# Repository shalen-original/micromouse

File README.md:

# Micromouse WiSe2021

## Project members:

* Philipp Hagenlocher
* Hendrik Möller
* Matteo Nardini
* Congnan "Jonas" Wang

## Goal and milestone:
The goal of this project is to build a micromouse from scatch and solve the maze challenge offerred by TUM. 

- [x] **22. Febuary: board design review** 
- [x] **1. March: board design fixed**
- [ ] **10.March: board ready**
- [ ] **31.March: project finshed**

## Maze definition:
>The micromouse maze shall comprise **16 x 16** multiples of an **18cm x 18cm** unit square.
The walls constituting the micromouse maze shall be **5cm high** and **1.2cm thick**. 

According to UK Micromouse Maze Solver Rules:
<https://www.cs.york.ac.uk/micromouse/Rules/Maze_Solver_Rules.pdf>

## Project functionalities

* PCB Design
* Hardware Design
* HAL
* Closed Loop Control
* Maze-solver
* Communication and UI

## TODOs

#### PCB design:
- [ ] Understand voltage regulator thermal details and pick the one that are actually needed

#### Hardware design:
- [ ] Pick the distance sensors
- [ ] Pick the HBridges

#### HAL:
- [ ] To be filled

#### Closed Loop Control:
- [x] Classify controll scenarios
	* Straight: 3 scenarios
		* corridor
		* one side opening
		* both sides opening
	* Turn: switch off distance sensors
	* Spin: switch off distance sensors
- [x] Determine controller types
	* PI controller
- [x] Determine motionControl APIs
	* move (rawVelocity)
	* turn (rawVelocity)
	* spin (rawVelocity)
	* update (xxx)
- [ ] Coding controllers in c#
	* [x] connect controller to HAL
	* [x] build PI controller
	* [ ] impliment control logic
		* [x] distance controller
		* [x] velocity controller
		* [x] Lookup table for pwm 
		* [ ] update()
		* [ ] upper limit for accumulated error of controllers
		* [ ] Error notification in error.h
	* [x] wire motionControl.h API with controllers
- [ ] Theory for tuning controller parameters 
- [ ] Debug controller on board

#### Maze-solver
- [x] Classic Flood Fill

#### Communication and UI
- [ ] To be filled

# Code Notation/Styling:
```
* Name Formatting:
	- functions: camelCase - getSomething()
	- `#define: CAPSLOCK_WITH_UNDERSCORE - CONFIG_H`
	- Variables: camelCase - timerInterruptFrequency
* Use "init" instead of "setup" (if there is no difference)
* Use in-line brackets only for "} else {" or similiar lines
* Code-Comments in-line for single important statements (or declarations)
* Code-Comments before function headers in c-file
* One empty line between sections of code, ordered as follows:
	- Header file: 
		Guard condition, 
		includes, 
		`#defines (namespace)`
		extern variable declarations
		function headers
	- C file: 
		includes,
		`#define (for constants)`
		member variables
		function implementations

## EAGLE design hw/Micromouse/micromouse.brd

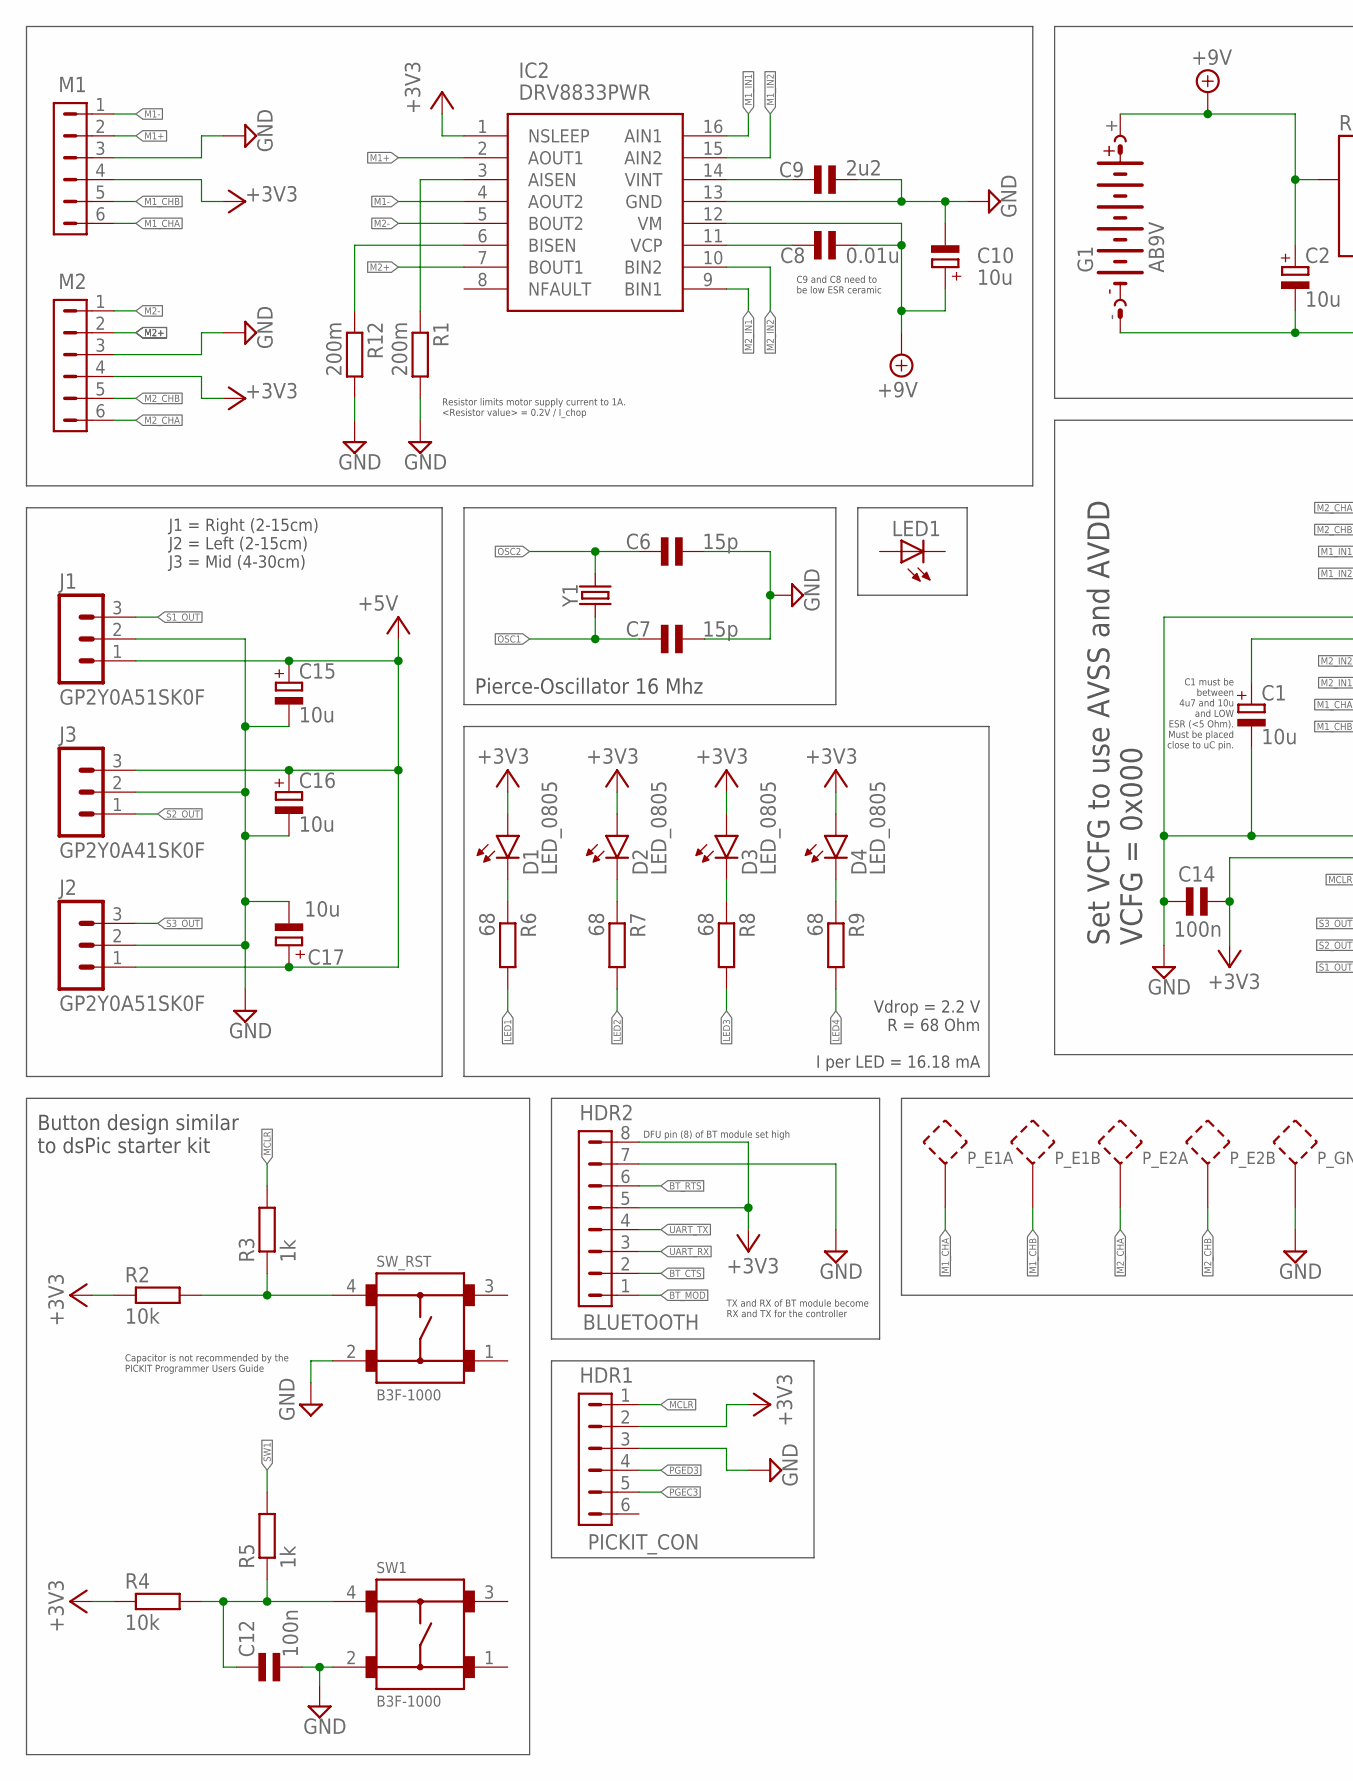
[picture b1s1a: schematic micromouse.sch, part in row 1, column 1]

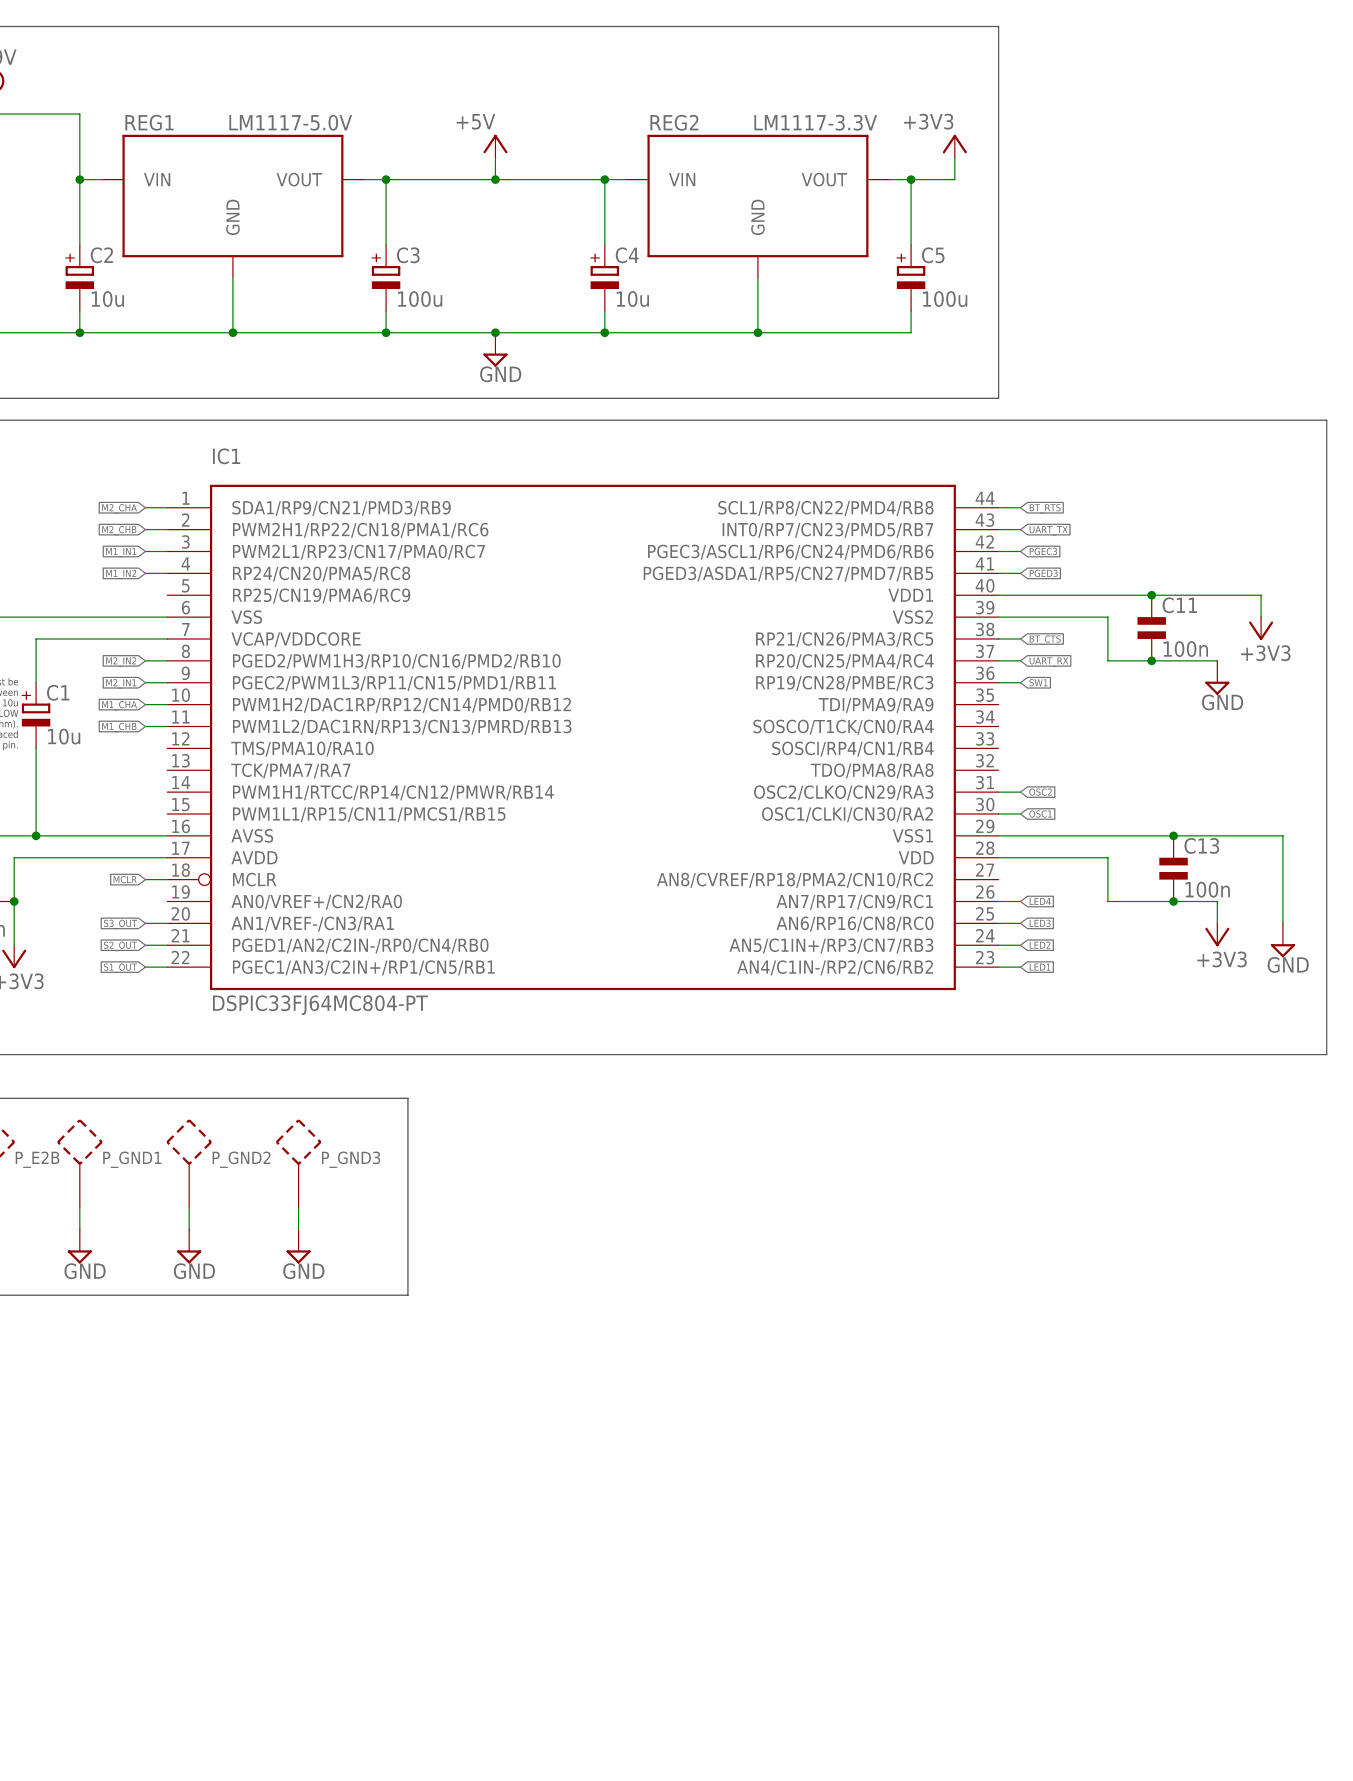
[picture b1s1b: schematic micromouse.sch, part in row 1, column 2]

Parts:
C1, C2, C4, C10, C15, C16, C17: 10u; 0805_POL
C3, C5: 100u; 0805_POL
C6, C7: 15p; 0805
C8: 0.01u; 0805
C9: 2u2; 0805
C11, C12, C13, C14: 100n; 0805
D1, D2, D3, D4: LED_0805; SMD_LED_0805
G1: AB9V
HDR1: PICKIT_CON; 6PIN
HDR2: BLUETOOTH; 1X08
IC1: DSPIC33FJ64MC804-PT; TQFP44
IC2: DRV8833PWR; SOP65P640X120-16N
J1, J2: GP2Y0A51SK0F; B3B-ZR(LF)(SN)
J3: GP2Y0A41SK0F; B3B-PH-K-S
LED1: LED5MM
M1, M2: MOTOR_CON; JP3Q
P_E1A, P_E1B, P_E2A, P_E2B: PROBE_POINTTHT; PROBEPOINT_THT
P_GND1, P_GND2, P_GND3: PROBE_POINTTHT; PROBEPOINT_THT
R1, R12: 200m; 0805
R2, R4: 10k; 0805
R3, R5: 1k; 0805
R6, R7, R8, R9: 68; 0805
REG1: LM1117-5.0V; SOT-223-4
REG2: LM1117-3.3V; SOT-223-4
SW1: B3F-1000
SW_RST: B3F-1000
Y1: CRYSTALPTH-HC49US; HC49US

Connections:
+3V3: C5.1 (+), C11.1 (+), C13.2 (-), C14.2 (-), D1.P$2 (A), D2.P$2 (A), D3.P$2 (A), D4.P$2 (A), HDR1.2, HDR2.5, HDR2.8, IC1.17 (AVDD), IC1.28 (VDD), IC1.40 (VDD1), IC2.1 (NSLEEP), M1.4, M2.4, R2.1, R4.1, REG2.2 (VOUT), REG2.4 (VOUT)
+5V: C3.1 (+), C4.1 (+), C15.1 (+), C16.1 (+), C17.1 (+), J1.1, J2.1, J3.3, REG1.2 (VOUT), REG1.4 (VOUT), REG2.3 (VIN)
+9V: C2.1 (+), C8.1 (+), C10.1 (+), G1.+, IC2.12 (VM), REG1.3 (VIN)
BT_CTS: HDR2.2, IC1.38 (RP21/CN26/PMA3/RC5)
BT_MOD: HDR2.1
BT_RTS: HDR2.6, IC1.44 (SCL1/RP8/CN22/PMD4/RB8)
GND: C1.2 (-), C2.2 (-), C3.2 (-), C4.2 (-), C5.2 (-), C6.2 (-), C7.2 (-), C9.2 (-), C10.2 (-), C11.2 (-), C12.2 (-), C13.1 (+), C14.1 (+), C15.2 (-), C16.2 (-), C17.2 (-), G1.-, HDR1.3, HDR2.7, IC1.6 (VSS), IC1.16 (AVSS), IC1.29 (VSS1), IC1.39 (VSS2), IC2.13 (GND), J1.2, J2.2, J3.2, M1.3, M2.3, P_GND1.P$1, P_GND2.P$1, P_GND3.P$1, R1.2, R12.2, REG1.1 (GND), REG2.1 (GND), SW1.2, SW_RST.2
LED1: IC1.23 (AN4/C1IN-/RP2/CN6/RB2), R6.2
LED2: IC1.24 (AN5/C1IN+/RP3/CN7/RB3), R7.2
LED3: IC1.25 (AN6/RP16/CN8/RC0), R8.2
LED4: IC1.26 (AN7/RP17/CN9/RC1), R9.2
M1+: IC2.2 (AOUT1), M1.2
M1-: IC2.4 (AOUT2), M1.1
M1_CHA: IC1.10 (PWM1H2/DAC1RP/RP12/CN14/PMD0/RB12), M1.6, P_E1A.P$1
M1_CHB: IC1.11 (PWM1L2/DAC1RN/RP13/CN13/PMRD/RB13), M1.5, P_E1B.P$1
M1_IN1: IC1.3 (PWM2L1/RP23/CN17/PMA0/RC7), IC2.16 (AIN1)
M1_IN2: IC1.4 (RP24/CN20/PMA5/RC8), IC2.15 (AIN2)
M2+: IC2.7 (BOUT1), M2.2
M2-: IC2.5 (BOUT2), M2.1
M2_CHA: IC1.1 (SDA1/RP9/CN21/PMD3/RB9), M2.6, P_E2A.P$1
M2_CHB: IC1.2 (PWM2H1/RP22/CN18/PMA1/RC6), M2.5, P_E2B.P$1
M2_IN1: IC1.9 (PGEC2/PWM1L3/RP11/CN15/PMD1/RB11), IC2.9 (BIN1)
M2_IN2: IC1.8 (PGED2/PWM1H3/RP10/CN16/PMD2/RB10), IC2.10 (BIN2)
MCLR: HDR1.1, IC1.18 (MCLR), R3.2
unnamed: IC2.6 (BISEN), R12.1
unnamed: D2.P$1 (C), R7.1
unnamed: C8.2 (-), IC2.11 (VCP)
unnamed: C9.1 (+), IC2.14 (VINT)
unnamed: IC2.3 (AISEN), R1.1
unnamed: C12.1 (+), R4.2, R5.1, SW1.4
unnamed: R2.2, R3.1, SW_RST.4
unnamed: D1.P$1 (C), R6.1
unnamed: D3.P$1 (C), R8.1
unnamed: D4.P$1 (C), R9.1
OSC1: C7.1 (+), IC1.30 (OSC1/CLKI/CN30/RA2), Y1.1
OSC2: C6.1 (+), IC1.31 (OSC2/CLKO/CN29/RA3), Y1.2
PGEC3: HDR1.5, IC1.42 (PGEC3/ASCL1/RP6/CN24/PMD6/RB6)
PGED3: HDR1.4, IC1.41 (PGED3/ASDA1/RP5/CN27/PMD7/RB5)
S1_OUT: IC1.22 (PGEC1/AN3/C2IN+/RP1/CN5/RB1), J1.3
S2_OUT: IC1.21 (PGED1/AN2/C2IN-/RP0/CN4/RB0), J3.1
S3_OUT: IC1.20 (AN1/VREF-/CN3/RA1), J2.3
SW1: IC1.36 (RP19/CN28/PMBE/RC3), R5.2
UART_RX: HDR2.3, IC1.37 (RP20/CN25/PMA4/RC4)
UART_TX: HDR2.4, IC1.43 (INT0/RP7/CN23/PMD5/RB7)
VCAP/VDDCORE: C1.1 (+), IC1.7 (VCAP/VDDCORE)

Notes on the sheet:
C1 must be between 4u7 and 10u and LOW ESR (<5 Ohm). Must be placed close to uC pin.
Pierce-Oscillator 16 Mhz
Resistor limits motor supply current to 1A. <Resistor value> = 0.2V / I_chop
Button design similar to dsPic starter kit
J1 = Right (2-15cm) J2 = Left (2-15cm) J3 = Mid (4-30cm)
Capacitor is not recommended by the PICKIT Programmer Users Guide
Set VCFG to use AVSS and AVDD VCFG = 0x000
TX and RX of BT module become RX and TX for the controller
DFU pin (8) of BT module set high
C9 and C8 need to be low ESR ceramic
Vdrop = 2.2 V R = 68 Ohm I per LED = 16.18 mA

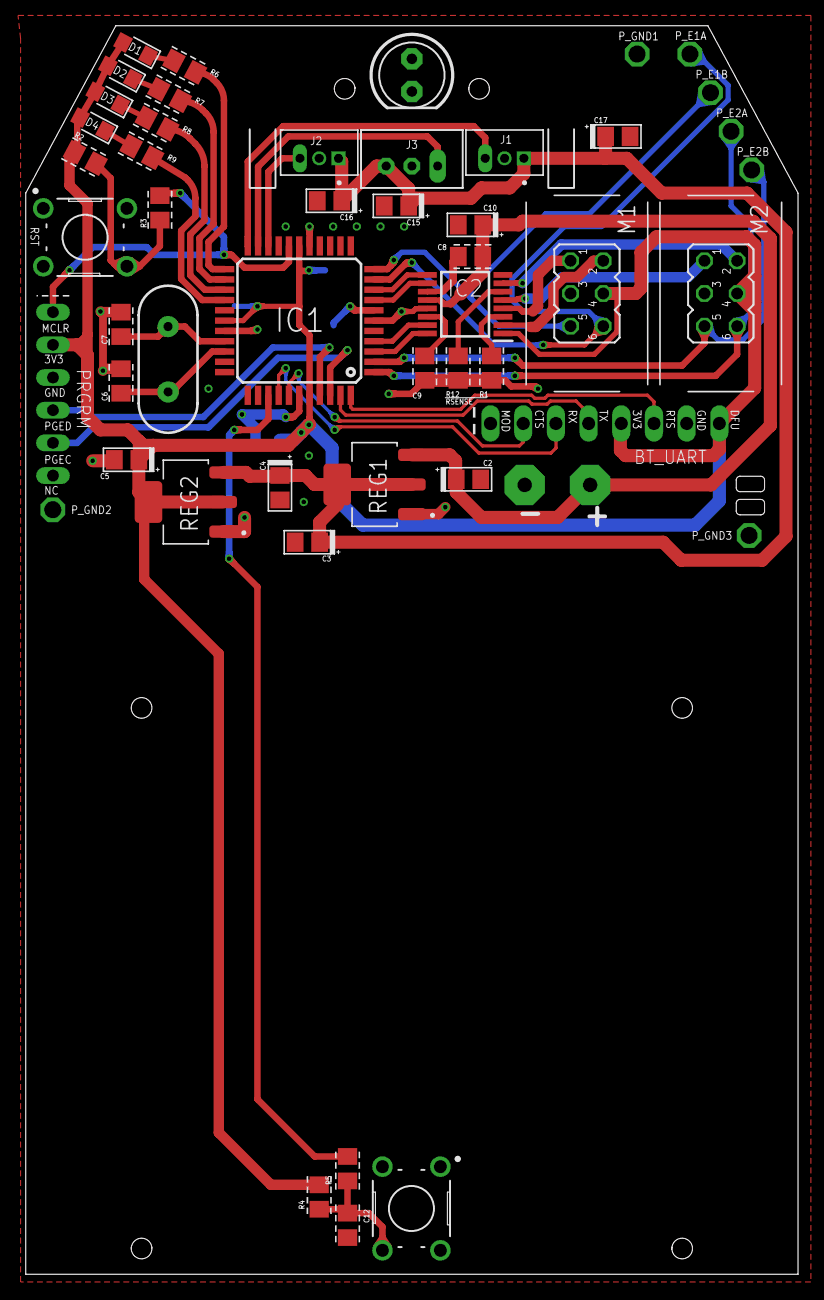
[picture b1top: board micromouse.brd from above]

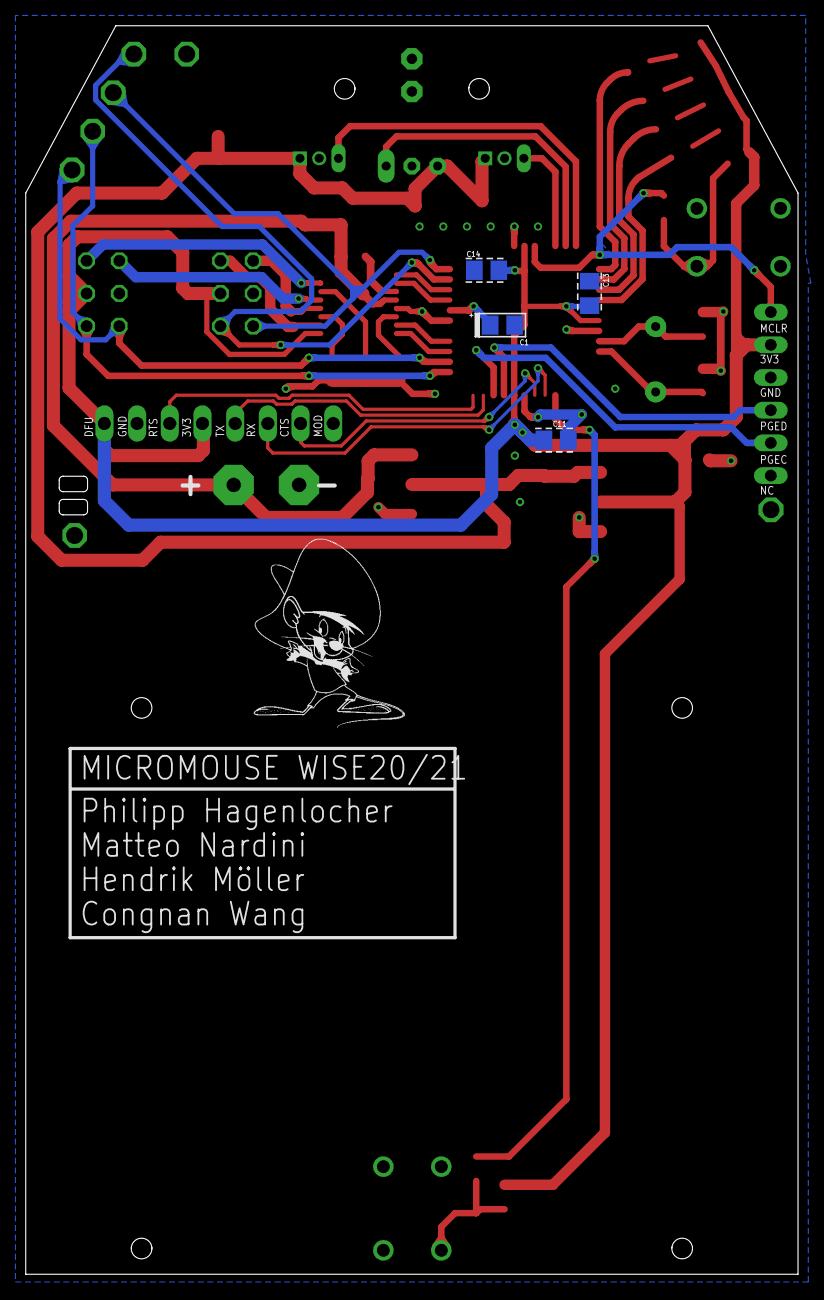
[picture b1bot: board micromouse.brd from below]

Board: 2 copper layers, 60.0 x 97.0 mm, 54 parts (4 on the bottom side), 44 nets.

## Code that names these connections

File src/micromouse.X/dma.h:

#ifndef DMA_H
#define	DMA_H

#include <xc.h>

#define RAW_SENSOR_RIGHT adcData[2]  // S1_OUT/AN3/RB1
#define RAW_SENSOR_FRONT adcData[1]  // S2_OUT/AN2/RB0
#define RAW_SENSOR_LEFT  adcData[0]  // S3_OUT/AN1/RA1

extern unsigned int adcData[32]__attribute__((space(dma)));

void initDMAChannel4(void);

#endif

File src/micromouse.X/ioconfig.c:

#include "xc.h"
#include "ioconfig.h"

void initIO()
{
    AD1PCFGL=0xFFFF; // Configure all pins to be digital
    
    // Configure the sensor pins to be analogue
    AD1PCFGLbits.PCFG1 = 0b0; // S3_OUT/AN1/RA1 is analougue
    AD1PCFGLbits.PCFG2 = 0b0; // S2_OUT/AN2/RB0 is analougue
    AD1PCFGLbits.PCFG3 = 0b0; // S1_OUT/AN3/RB1 is analougue
    
    // Configure the sensor pins to be input
    TRISAbits.TRISA1 = 0b1; // S3_OUT/AN1/RA1 is input
    TRISBbits.TRISB0 = 0b1; // S2_OUT/AN2/RB0 is input
    TRISBbits.TRISB1 = 0b1; // S1_OUT/AN3/RB1 is input
    
    // Configure LEDs to be outputs
    LATBbits.LATB2 = 0b0;
    LATBbits.LATB3 = 0b0;
    LATCbits.LATC0 = 0b0;
    LATCbits.LATC1 = 0b0;
    
    // Configure buttons to be inputs
    TRISCbits.TRISC3 = 0b1;
    
    // Remap pins (see tables 11-1 and 11-2 on the datasheet)
    __builtin_write_OSCCONL(OSCCON & 0xbf);
    
        // QEI1 -> Left Motor (M1)
        RPINR14bits.QEA1R = 12; //QEI1A -> RP12/M1_CHA
        RPINR14bits.QEB1R = 23; //QEI1B -> RP13/M1_CHB

        // QEI2 -> Right Motor (M2)
        RPINR16bits.QEA2R = 9; //QEI2A -> RP9/M2_CHA
        RPINR16bits.QEB2R = 22; //QEI2B -> RP22/M2_CHB

        // UART
        RPINR18bits.U1RXR = 20; //U1RX -> RP20/UART_RX
        RPINR18bits.U1CTSR = 21; //U1CTS -> RP21/BT_CTS
        RPOR3bits.RP7R = 0b00011; //U1TX -> RP7/UART_TX
        RPOR4bits.RP8R = 0b00100; //U1RTS -> RP8/BT_RTS
        
#ifdef SOFTWARE_FIX
        //Output compare
        RPOR11bits.RP23R = 0b10010; //OC1 -> RP23/M1_IN1
        RPOR12bits.RP24R = 0b10011; //OC2 -> RP24/M1_IN2
#endif

    __builtin_write_OSCCONL(OSCCON | 0x40);
     
    int i;
    for (i = 0; i < 30000; i++); // short dirty delay for changes to take effect
}

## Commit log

2021-01-13 Uploaded the draw.io hardware diagram
2021-01-16 Added EAGLE project
2021-01-16 Added BOM.ods
2021-01-18 Added voltage regulators and sensors to BOM
2021-01-18 Added JST PH components
2021-01-18 init first commit of MPLAB system added code styling (not finished!) to the README.md
2021-01-19 added mc_datasheet.pdf
2021-01-19 Added capacitors to BOM
2021-01-21 Added datasheets relating to oscillators
2021-01-21 Added voltage regulator circuit; Added oscillator configuration; Added parts to library
2021-01-21 moved mc_datasheet.pdf into datasheet folder
2021-01-21 made folder for MC datasheets, added an errata and mc_pin.png
2021-01-21 fixed mc_pin.png
2021-01-22 Added LM1117 datasheet
2021-01-24 exported general structs and enum into utils.h (temporally)
2021-01-24 added maze.h and maze.c with rough setup of high-level software approach
2021-01-24 added robotControl.c which is a rough foundation for the mid-level robot control system
2021-01-26 added timer2.c
2021-01-26 exported position from utils.h into position.c
2021-01-27 Added PICkit programmer datasheet
2021-01-27 Updated schematic
2021-01-28 PIcontroller-build
2021-01-28 PIcontroller-build-fix
2021-01-28 PIcontroller-update
2021-01-29 Added sensor datasheet
2021-01-29 extracted direction.c from utils.h, implemented helper functions
2021-01-29 added motionControl.c as mid-level with robotControl.c being above it. made necessary adjustments
2021-01-29 fixed some includes (previous commit does NOT compile!)
2021-01-29 merge-conflict manually made commit
2021-01-29 fixed merge part 2
2021-01-29 controldiagram-upload
2021-02-02 Updated EAGLE project
2021-02-02 Fixed datasheet name
2021-02-02 Added motor datasheets
2021-02-02 First routing on PCB
2021-02-03 Cleanup on PCB routing
2021-02-03 Updated PCB
2021-02-04 Added Bluetooth module
2021-02-10 Added LED datasheet
2021-02-10 Tighter layout for PCB; Removed transistors for LEDs
2021-02-16 Added hole for routing wires of battery connector
2021-02-18 Tidied up schematic
2021-02-18 Updated silkscreen
2021-02-19 Added silkscreen; Added more space between parts; Added testpoints
2021-02-19 Software diagram
2021-02-19 update motionControl diagram
2021-02-23 Added current sense resistor datasheet
2021-02-23 Tweaked schematic and PCB
2021-02-24 Added probing points for GND; Small tweaks
2021-02-24 Begun consolidating HAL
2021-02-24 Fixed analogue pin configuration
2021-02-24 Fixed stupid C
2021-02-24 Better errors
2021-02-24 Proposal for motor HAL API
2021-02-25 Changes to the board according to design review
2021-02-26 Added order listing
2021-02-26 Added battery clip to order
2021-02-26 Changed resistor values for LEDS
2021-02-26 Deleted BOM.ods
2021-02-27 Updated Order
2021-03-02 Finalized board; Added speedy gonzales in the process!
2021-03-03 reorganize controller code
2021-03-03 define struct sperately for velocity controllers and distance controllers
2021-03-03 initialize distance controller in timer 1 and modify APIs in motionControl.c
2021-03-04 motionControl.h API modified, distance controller implimented
2021-03-05 added mazeControl.c (implemented classic floodfill there) extracted boolean definition into its own header fixed some dependancies at this point: call getNewRaceDirection(position curPos) to receive 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
2021-03-08 Added HAL for motors
2021-03-08 Added QEI and fixed build
2021-03-08 Timers
2021-03-08 Implemented buttons
2021-03-08 Implemented LEDs
2021-03-09 Fixed ioconfig
2021-03-09 uart
2021-03-11 replace robotControl.c with directionControl.c still undone and untested (the actual commands for motioncontrol missing)
2021-03-11 init commit of mazeSolverSimulator
2021-03-13 Fixed PWM (if hardware fix available)
2021-03-13 Added pin mapping for UART
2021-03-13 Implemented SOFTWARE_FIX for the PWM problem
2021-03-13 Fixed PWM duty cycle computation and overrides
2021-03-13 updated decision map of direction control implemented first dummmy-calls from direction control to motion control (TODO speed values)
2021-03-13 velocity controller implimented
2021-03-13 update roadmap
2021-03-14 directionControl.c now uses updateStruct.h
2021-03-14 update() implimented
2021-03-14 connect to updateStruct.h
2021-03-14 modification on start position recording functionalities of motionControl
2021-03-15 directionControl.c now incoroporates the IDLE state minor fixes
2021-03-15 Added way of communicating with Adafruit module
2021-03-15 Improved some diagrams
2021-03-16 added very simple and rough hug-right-wall exploration mode algorithm (todo: polishing)
2021-03-16 minor fixes
2021-03-16 added update() call from distanceControl to DirectionControl
2021-03-16 added an easier position instantion function as well as a function to add two positions
2021-03-16 made maze.c simpler (extracted constants into defines) changed main.c accordingly (and added initDirectionControl() call)
2021-03-16 Replaced LED datasheet
2021-03-17 major rework of direction control: - clockwise direction is now positive angle (not negative) - wallchange does affect distance passed check - exported many things into defines - initialization with 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
2021-03-17 minor change
2021-03-17 minor changes: ensure distance controller will not be activated while turn() and spin()
2021-03-17 fixed the IDLE to non-IDLE issue with wallchange (walls == 0 now means that the next wallchange update does not trigger movement related things)
2021-03-17 minor fix
2021-03-18 made the wallchange skip state better (with define)
2021-03-19 Added osc. datasheet
2021-03-23 uart commands implemented: - directionControl.c IDLE toggle now in one function - hashfunction on uart.c - minor fixes
2021-03-23 added comments to utils.h
2021-03-30 Fixed distance controller set point
2021-05-19 Added final report
2021-09-15 README

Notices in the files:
parts and their libraries:
SparkFun-Clocks: Licensing: Creative Commons ShareAlike 4.0 International - https://creativecommons.org/licenses/by-sa/4.0
